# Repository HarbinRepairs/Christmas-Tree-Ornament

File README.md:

## PCB Christmas Tree Ornament
This is a Christmas tree ornament designed by Harbin Repairs using a 4013 based chaser circuit. There are 2-3 LED's per channel, that means there are ony 2-3 LED's turned on at a time to save battery power, this also makes it appear to be more random than 8 channels. Also the LED's have carefully picked colors and number of LED's per channel to ensure the LED's don't draw too much current resulting in half dim LED's. 

Want one assembled? Get it here:

Our store: https://bit.ly/2Tyu0G7
Ebay: https://www.ebay.com/itm/264097266703

### Issues
On this version there is a pad for a micro USB conector but it won't work unless you solder the diode on D26, unfortunately we used the wrong pad so you will need to change it, otherwise if you just bridge that footprint then the 5v from the USB connector will go straight to the battery with no protection (BAD THINGS WILL HAPPEN). There was no intention of charging the battery over USB, however you can power the ornament from USB with D26 bridged just don't do it with a battery installed.

### LED Color Locations
This is correct location for each color of the LED's, if they are not soldered in this configuration then some of the LED's will be too dim or too bright.

### Bill Of Materials

https://github.com/HarbinRepairs/Christmas-Tree-Ornament/blob/master/Bill%20Of%20Materials.csv

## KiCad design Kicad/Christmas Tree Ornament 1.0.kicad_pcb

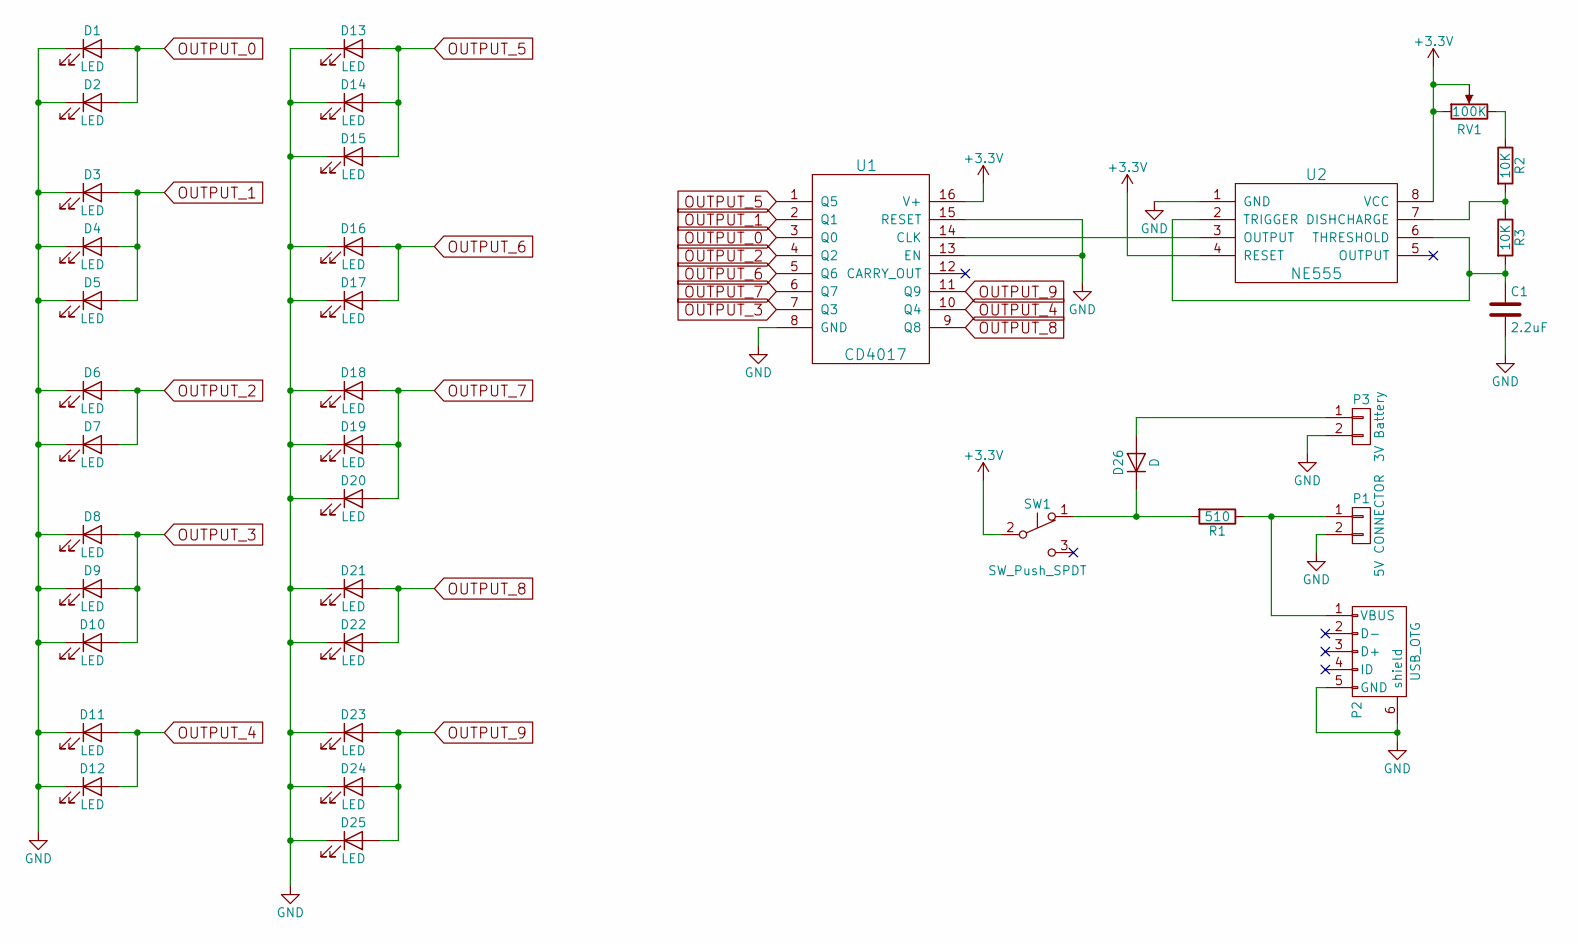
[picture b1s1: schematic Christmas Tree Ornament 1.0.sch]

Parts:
C1: 2.2uF; C_0805
D1, D2, D3, D4, D5, D6, D7, D8, D9, D10, D11, D12, D13, D14, D15, D16, D17, D18, D19, D20, D21, D22, D23, D24, D25: LED; LED_0805
D26: D; D_0805
P1: 5V CONNECTOR; NetTie-I_SMD
P2: USB_OTG; USB_Micro-B
P3: 3V Battery; CR2032H
R1: 510; R_0805
R2, R3: 10K; R_0805
RV1: 100K; Potentiometer_Trimmer-EVM3E
SW1: SW_Push_SPDT; SW_SPDT_3P_11.1mm_5.5mm
U1: CD4017; SO-16-N
U2: NE555; SOIC-8-N

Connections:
+3V3: RV1.1, RV1.2, SW1.2 (B), U1.16 (V+), U2.4 (RESET), U2.8 (VCC)
GND: C1.2, D1.1 (K), D2.1 (K), D3.1 (K), D4.1 (K), D5.1 (K), D6.1 (K), D7.1 (K), D8.1 (K), D9.1 (K), D10.1 (K), D11.1 (K), D12.1 (K), D13.1 (K), D14.1 (K), D15.1 (K), D16.1 (K), D17.1 (K), D18.1 (K), D19.1 (K), D20.1 (K), D21.1 (K), D22.1 (K), D23.1 (K), D24.1 (K), D25.1 (K), P1.2, P2.5 (GND), P2.6 (shield), P3.2, U1.8 (GND), U1.13 (EN), U1.15 (RESET), U2.1 (GND)
unnamed: C1.1, R3.2, U2.2 (TRIGGER), U2.6 (THRESHOLD)
unnamed: D26.1 (K), R1.2, SW1.1 (A)
unnamed: D26.2 (A), P3.1
unnamed: P1.1, P2.1 (VBUS), R1.1
unnamed: R2.1, RV1.3
unnamed: R2.2, R3.1, U2.7 (DISHCHARGE)
unnamed: U1.14 (CLK), U2.3 (OUTPUT)
OUTPUT_0: D1.2 (A), D2.2 (A), U1.3 (Q0)
OUTPUT_1: D3.2 (A), D4.2 (A), D5.2 (A), U1.2 (Q1)
OUTPUT_2: D6.2 (A), D7.2 (A), U1.4 (Q2)
OUTPUT_3: D8.2 (A), D9.2 (A), D10.2 (A), U1.7 (Q3)
OUTPUT_4: D11.2 (A), D12.2 (A), U1.10 (Q4)
OUTPUT_5: D13.2 (A), D14.2 (A), D15.2 (A), U1.1 (Q5)
OUTPUT_6: D16.2 (A), D17.2 (A), U1.5 (Q6)
OUTPUT_7: D18.2 (A), D19.2 (A), D20.2 (A), U1.6 (Q7)
OUTPUT_8: D21.2 (A), D22.2 (A), U1.9 (Q8)
OUTPUT_9: D23.2 (A), D24.2 (A), D25.2 (A), U1.11 (Q9)

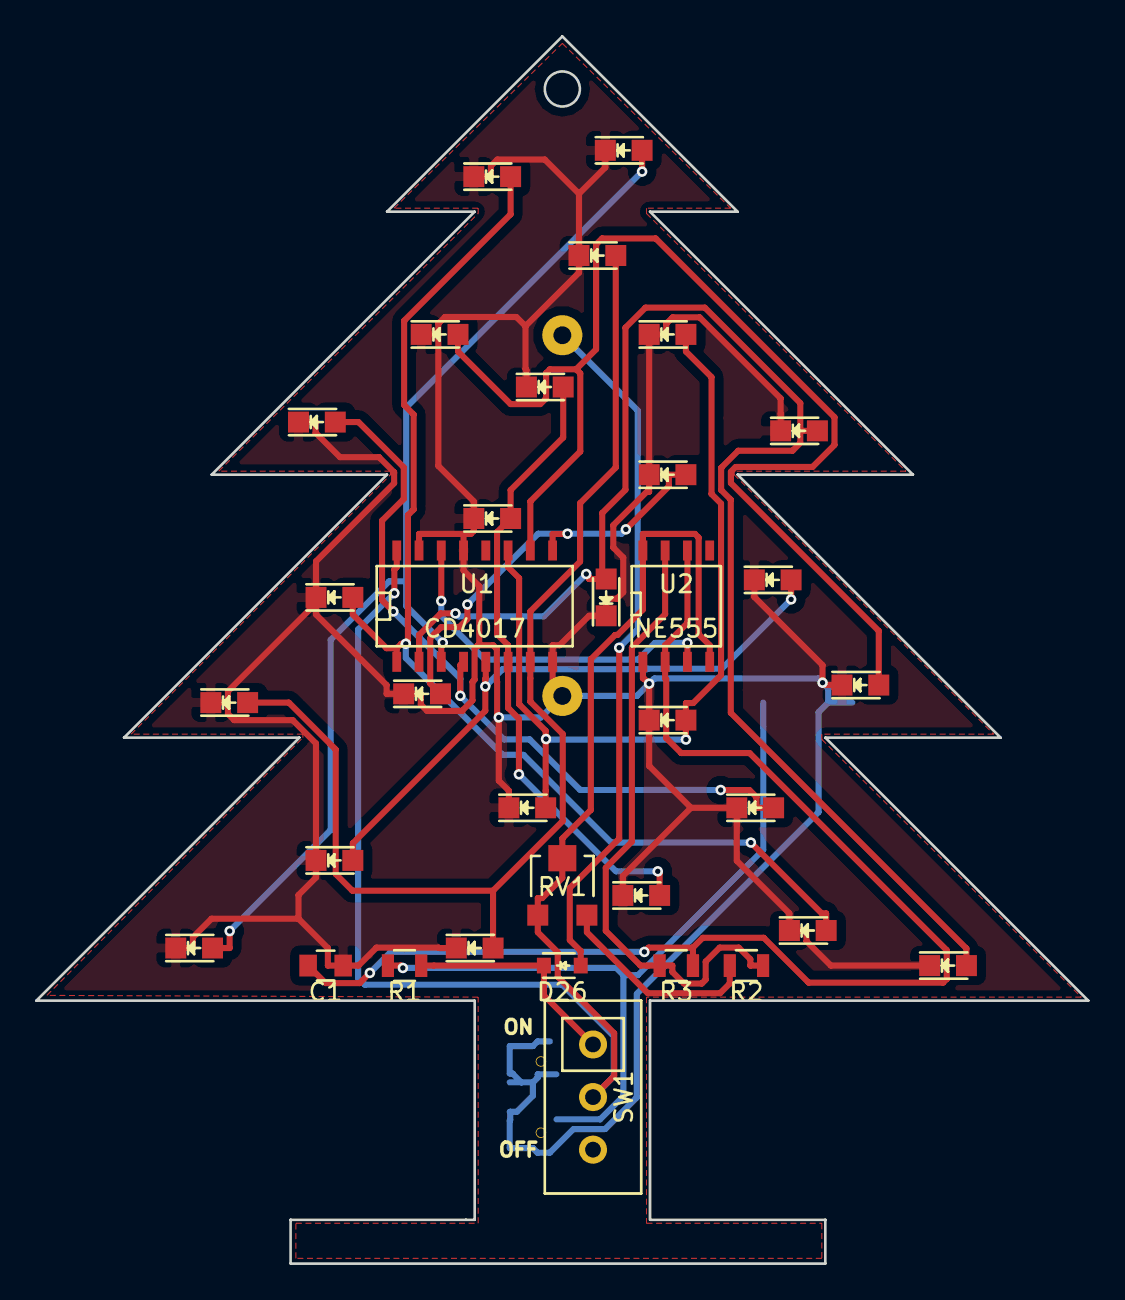
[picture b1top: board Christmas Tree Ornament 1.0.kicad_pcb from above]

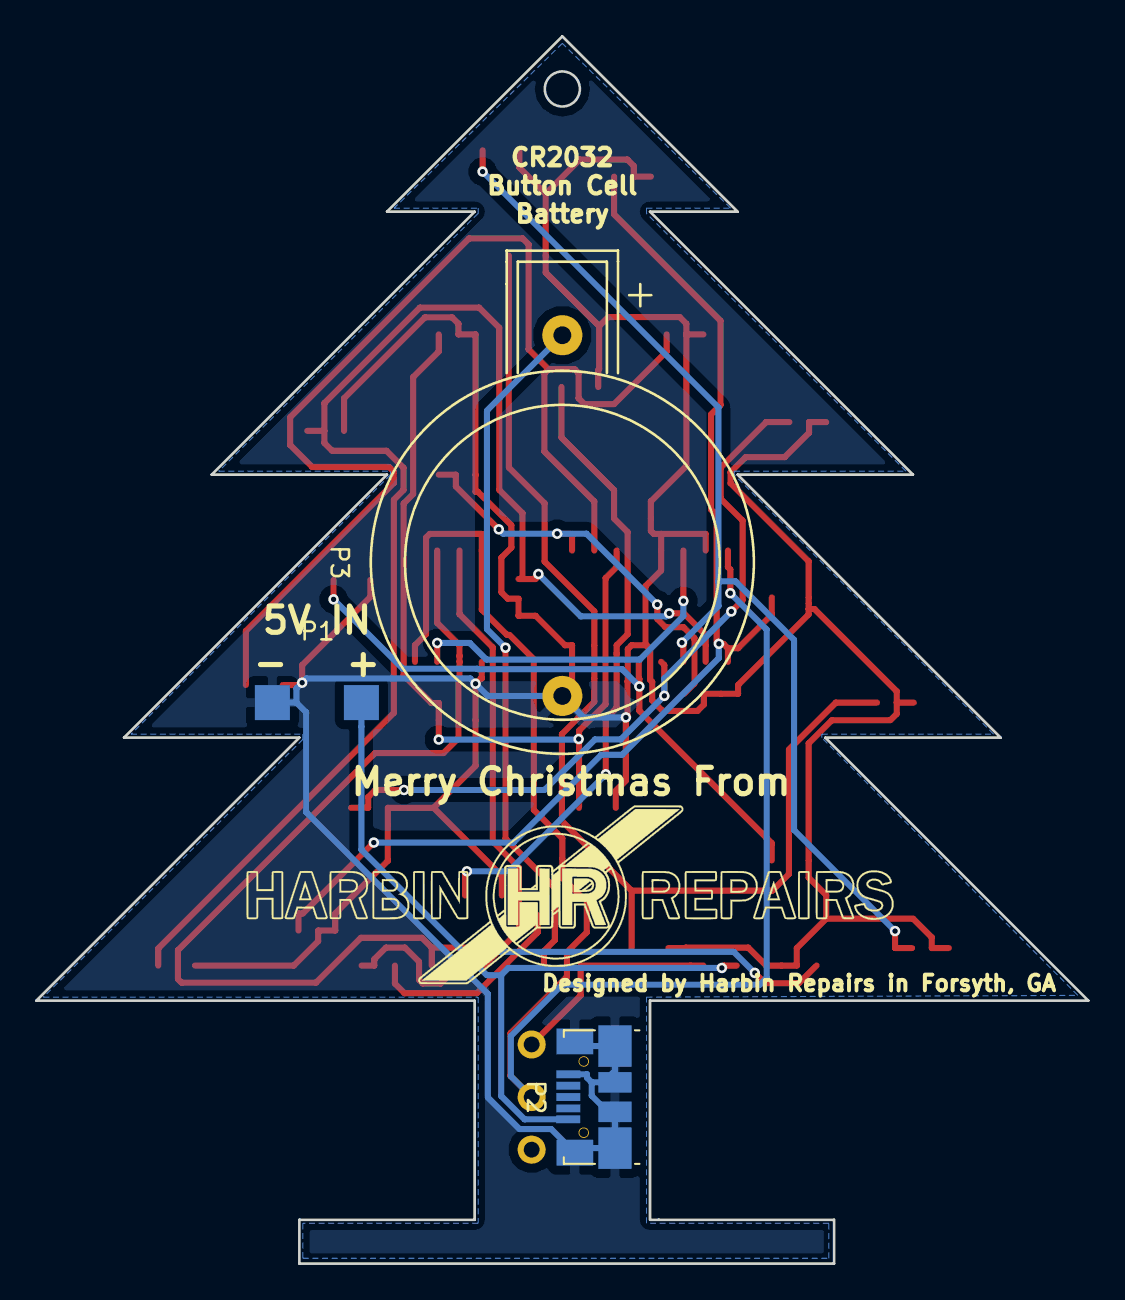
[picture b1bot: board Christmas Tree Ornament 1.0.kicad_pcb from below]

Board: 2 copper layers, 60.0 x 70.0 mm, 37 parts (3 on the bottom side), 19 nets.
